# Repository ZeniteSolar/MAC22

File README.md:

# MAC22
Modulo de acionamento da contatora 2022

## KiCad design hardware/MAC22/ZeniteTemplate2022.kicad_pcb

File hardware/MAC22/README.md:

# MSC19
Voltage or Current Sensor Module for CANBUS with ATmega328p

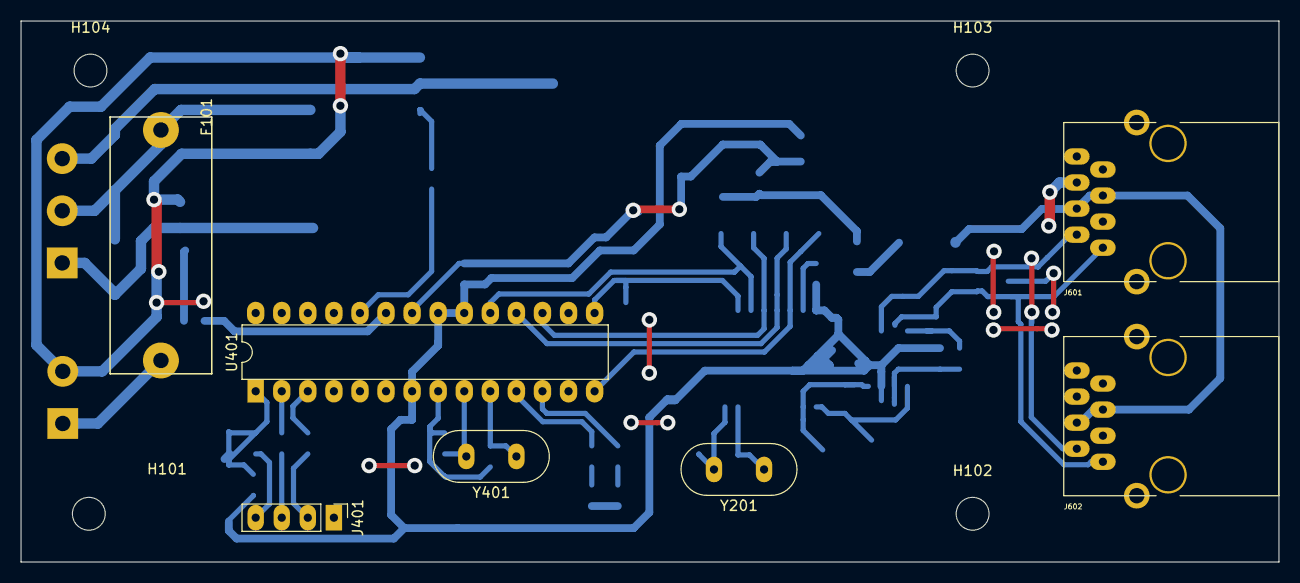
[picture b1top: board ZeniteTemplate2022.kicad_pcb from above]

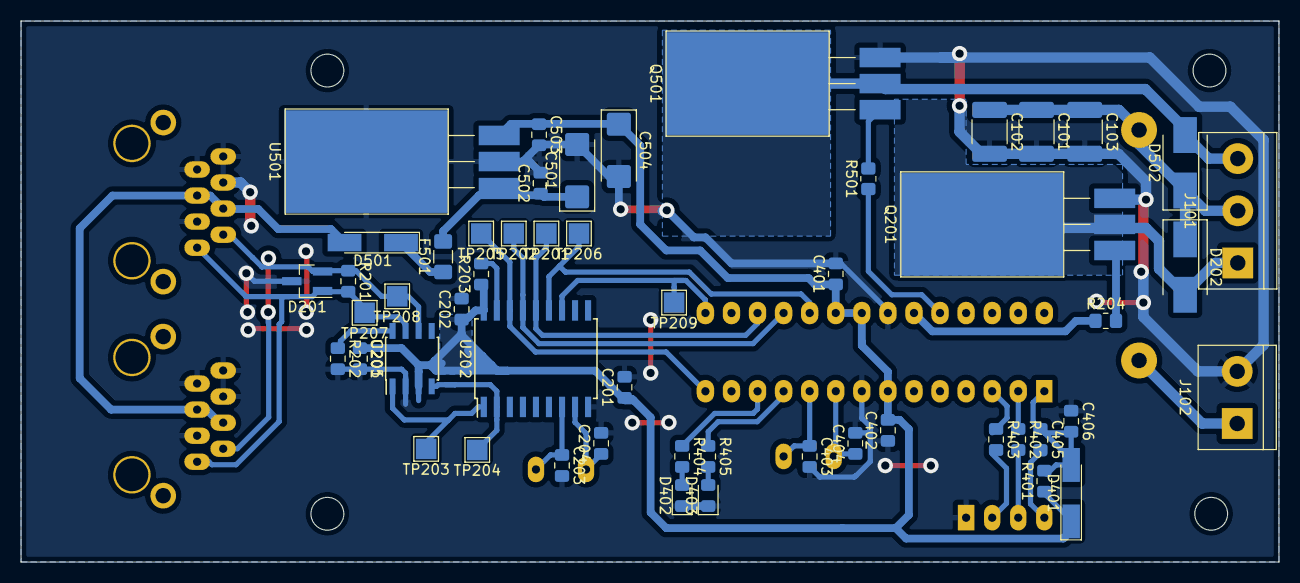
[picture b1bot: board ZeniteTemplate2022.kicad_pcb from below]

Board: 2 copper layers, 122.6 x 52.7 mm, 63 parts (52 on the bottom side), 38 nets.

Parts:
C101, C102, C103: 4.7uF; C_1812_4532Metric_Pad1.57x3.40mm_HandSolder
C201, C202, C205, C401, C402, C405, C406, C502, C503: 100nF; C_0805_2012Metric_Pad1.15x1.40mm_HandSolder
C203, C204, C403, C404: 22pF; C_0805_2012Metric_Pad1.15x1.40mm_HandSolder
C501, C504: 1uF; CP_EIA-6032-20_AVX-F_Pad2.25x2.35mm_HandSolder
D201: pesd1can; SOT-23_Handsoldering
D202, D502: 3A; D_SMB_Handsoldering
D401, D501: LL4148; D_MiniMELF_Handsoldering
D402, D403: LED_RED; LED_0805_2012Metric_Pad1.15x1.40mm_HandSolder
F101: 3A; Fuse_Holder_5x20
F501: 500mA; Fuse_1206_3216Metric_Pad1.42x1.75mm_HandSolder
H101, H102, H103, H104: MountingHole; MountingHole_3.2mm_M3
J101: Conn_01x03; TerminalBlock_bornier-3_P5.08mm
J102: +12V; TerminalBlock_bornier-2_P5.08mm
J401: USART; PinHeader_1x04_P2.54mm_Vertical
J601, J602: RJ45; RJ45_YH59_01
Q201, Q501: IRF530; TO-220-3_Horizontal_TabDown_SMD
R201: 120; R_0805_2012Metric_Pad1.15x1.40mm_HandSolder
R202: 4k7; R_0805_2012Metric_Pad1.15x1.40mm_HandSolder
R203, R401: 10k; R_0805_2012Metric_Pad1.15x1.40mm_HandSolder
R204, R501: 100; R_0805_2012Metric_Pad1.20x1.40mm_HandSolder
R402, R403, R404, R405: 1k; R_0805_2012Metric_Pad1.15x1.40mm_HandSolder
TP201: SI; TestPoint_Pad_2.0x2.0mm
TP202: SO; TestPoint_Pad_2.0x2.0mm
TP203: TXCAN; TestPoint_Pad_2.0x2.0mm
TP204: RXCAN; TestPoint_Pad_2.0x2.0mm
TP205: SC; TestPoint_Pad_2.0x2.0mm
TP206: SCK; TestPoint_Pad_2.0x2.0mm
TP207: CAN_H; TestPoint_Pad_2.0x2.0mm
TP208: CAN_L; TestPoint_Pad_2.0x2.0mm
TP209: INT; TestPoint_Pad_2.0x2.0mm
U201: MCP2551-I/SN; SOIC-8_3.9x4.9mm_P1.27mm
U202: MCP2515-xSO; SOIC-18W_7.5x11.6mm_P1.27mm
U401: ATMEGA328P-PU; DIP-28_W7.62mm
U501: LM7805; TO-220-3_Horizontal_TabDown_SMD
Y201, Y401: 16MHz; Crystal_HC49-U_Vertical

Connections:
+5V: C201.1, C202.1, C205.1, C401.1, C402.2, C503.1, C504.1, D401.1 (K), R203.1, R401.1, U201.3 (VDD), U202.18 (VDD), U401.7 (VCC), U401.20 (AVCC), U401.21 (AREF), U501.3 (VO)
+12V: C101.1, C102.1, C103.1, D202.1 (K), D502.1 (K), F101.1, J101.2
/CANBUS CONN/CAN_18V: D501.2 (A), J601.4, J601.5, J602.4, J602.5
/CANBUS CONN/CAN_H: D201.1 (A1), J601.1, J602.1, R201.2, TP207.1, U201.7 (CANH)
/CANBUS CONN/CAN_L: D201.2 (A2), J601.2, J602.2, R201.1, TP208.1, U201.6 (CANL)
/CANBUS/RXCAN: TP204.1, U201.4 (RXD), U202.2 (RXCAN)
/CANBUS/TXCAN: TP203.1, U201.1 (TXD), U202.1 (TXCAN)
/MCU/LED1: R405.1, U401.11 (PD5)
/MCU/LED2: R404.1, U401.12 (PD6)
/MCU/MCP_INT: TP209.1, U202.12 (~INT), U401.15 (PB1)
/MCU/MCP_SS: TP205.1, U202.16 (~CS), U401.14 (PB0)
/MCU/ONCoil1: R204.1, U401.23 (PC0)
/MCU/ONCoil2: R501.1, U401.24 (PC1)
/MCU/RESET: C405.1, C406.2, D401.2 (A), R401.2, U401.1 (~RESET/PC6)
/MCU/USART_RX: R402.1, U401.2 (PD0)
/MCU/USART_TX: R403.1, U401.3 (PD1)
/MISO: TP202.1, U202.15 (SO), U401.18 (PB4)
/MOSI: TP201.1, U202.14 (SI), U401.17 (PB3)
/POWER SUPPLY/+18V_OUT: C501.1, C502.1, F501.2, U501.1 (VI)
/SCK: TP206.1, U202.13 (SCK), U401.19 (PB5)
/coil1_drive/Coil-: D502.2 (A), J101.3, Q501.2 (D)
/coil2_drive/Coil-: D202.2 (A), J101.1, Q201.2 (D)
GND: C101.2, C102.2, C103.2, C201.2, C202.2, C203.2, C204.2, C205.2, C401.2, C402.1, C403.2, C404.2, C406.1, C501.2, C502.2, C503.2, C504.2, D201.3 (common), D402.1 (K), D403.1 (K), J102.2, J401.1, J601.3, J601.6, J601.7, J601.8, J602.3, J602.6, J602.7, J602.8, Q201.3 (S), Q501.3 (S), R202.2, U201.2 (VSS), U202.9 (VSS), U401.8 (GND), U401.22 (GND), U501.2 (GND)
unnamed: C203.1, U202.7 (OSC2), Y201.1
unnamed: C204.1, U202.8 (OSC1), Y201.2
unnamed: C403.1, U401.10 (XTAL2/PB7), Y401.1
unnamed: C404.1, U401.9 (XTAL1/PB6), Y401.2
unnamed: C405.2, J401.4
unnamed: D402.2 (A), R404.2
unnamed: D403.2 (A), R405.2
unnamed: D501.1 (K), F501.1
unnamed: F101.2, J102.1
unnamed: J401.2, R403.2
unnamed: J401.3, R402.2
unnamed: Q201.1 (G), R204.2
unnamed: Q501.1 (G), R501.2
unnamed: R202.1, U201.8 (STBY)
unnamed: R203.2, U202.17 (~RESET)

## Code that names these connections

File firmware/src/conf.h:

/**
 * @file conf.h
 *
 * @defgroup CONF Configurations
 *
 * @brief General configuration of the system.
 *
 * @{
 */

#ifndef CONF_H
#define CONF_H

#ifndef F_CPU
#define F_CPU 16000000UL    //define a frequencia do microcontrolador - 16MHz
#endif /* ifndef F_CPU */


// CONFIGURACOES DE COMPILACAO
#define DEBUG_ON
#define VERBOSE_ON
#define VERBOSE_ON_CAN_APP
//#define VERBOSE_ON_MACHINE
//#define VERBOSE_ON_ADC
#define VERBOSE_ON_INIT
#define VERBOSE_ON_ERROR
//#define PRINT_INFOS

#define CAN_SIGNATURE_SELF      CAN_SIGNATURE_MAC22
#define CAN_MASK                0b11111111111

// MODULES ACTIVATION
#define USART_ON
#define CAN_ON
#define CAN_DEPENDENT
// #define ADC_ON
#define MACHINE_ON
#define LED_ON
#define WATCHDOG_ON
//#define SLEEP_ON
#define CONTACTOR_ON

#ifdef CONTACTOR_ON
#define CONTACTOR_FORWARD_COIL PC0
#define CONTACTOR_REVERSE_COIL PC1
#define CONTACTOR_DDR DDRC
#define CONTACTOR_PIN PINC
#define CONTACTOR_PORT PORTC
#endif

#ifdef MACHINE_ON
#define MACHINE_TIMER_FREQUENCY             300           //<! machine timer frequency in Hz
#define MACHINE_TIMER_PRESCALER             1024          //<! machine timer prescaler
#define MACHINE_FREQUENCY                   100           //<! machine frequency in Hz
#define MACHINE_CLK_DIVIDER_VALUE           (MACHINE_TIMER_FREQUENCY)/(MACHINE_FREQUENCY)  //<! machine_run clock divider
#endif // MACHINE_ON

#ifdef LED_ON
#define     LED_PORT                PORTD
#define     LED_PIN                 PIND
#define     LED_DDR                 DDRD
#define     LED1                    PD5
#define     LED2                    PD6
#define     cpl_led(y)              cpl_bit(LED_PORT, y)
#define     set_led(y)              set_bit(LED_PORT, y)
#define     clr_led(y)              clr_bit(LED_PORT, y)
#else
#define     cpl_led()
#define     set_led()
#define     clr_led()
#endif // LED_ON


#ifdef CAN_ON
#define SPI_ON
#define CAN_APP_SEND_STATE_FREQ             10//36000     //<! state msg frequency in Hz

// CANBUS DEFINITONS
// ----------------------------------------------------------------------------
/* Global settings for building the can-lib and application program.
 *
 * The following two #defines must be set identically for the can-lib and
 * your application program. They control the underlying CAN struct. If the
 * settings disagree, the underlying CAN struct will be broken, with
 * unpredictable results.
 * If can.h detects that any of the #defines is not defined, it will set them
 * to the default values shown here, so it is in your own interest to have a
 * consistent setting. Ommiting the #defines in both can-lib and application
 * program will apply the defaults in a consistent way too.
 *
 * Select if you want to use 29 bit identifiers.
 */
#define	SUPPORT_EXTENDED_CANID	0

/* Select if you want to use timestamps.
 * Timestamps are sourced from a register internal to the AT90CAN.
 * Selecting them on any other controller will have no effect, they will
 * be 0 all the time.
 */
#define	SUPPORT_TIMESTAMPS		0

#endif // CAN_ON

/**
 * @}
 */

#endif /* ifndef CONF_H */

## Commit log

2022-02-26 final version PCB
2022-02-26 First version of firmware, derived from MCB19.
2022-02-26 Fix can dependency: was expecting MIC ID, but should be MAM.
2022-02-26 Reset contactor in every state other than running
2022-02-26 Fix: initialize both coils PORD/DDR
2022-02-26 hardware temporary
